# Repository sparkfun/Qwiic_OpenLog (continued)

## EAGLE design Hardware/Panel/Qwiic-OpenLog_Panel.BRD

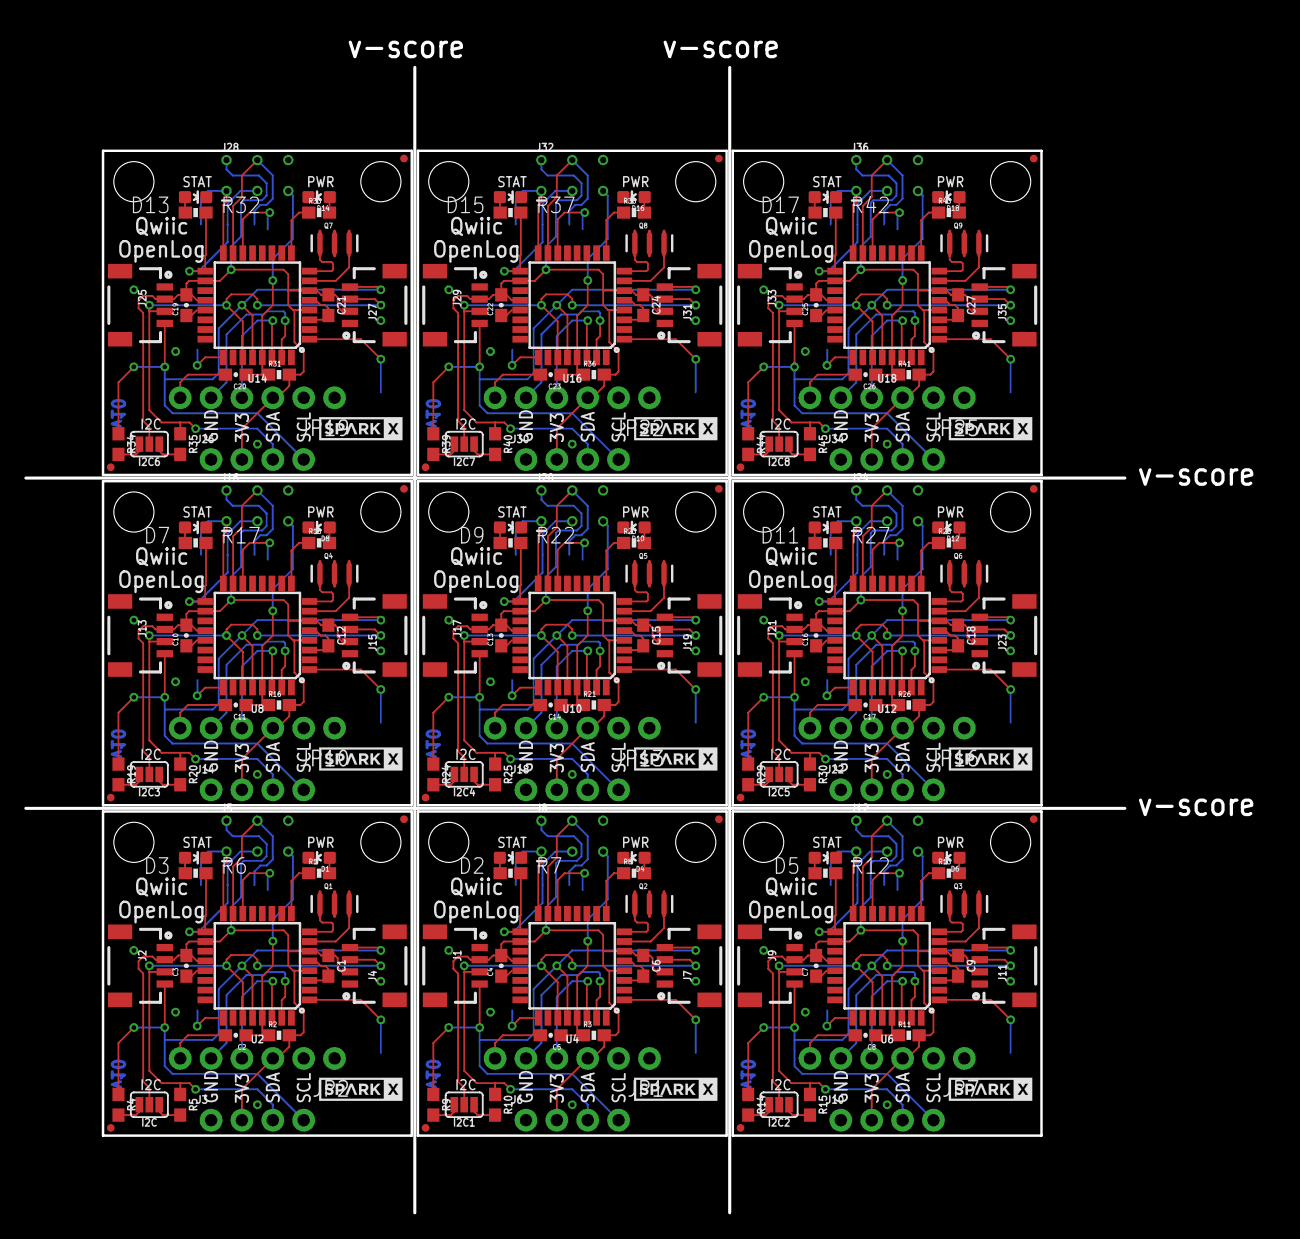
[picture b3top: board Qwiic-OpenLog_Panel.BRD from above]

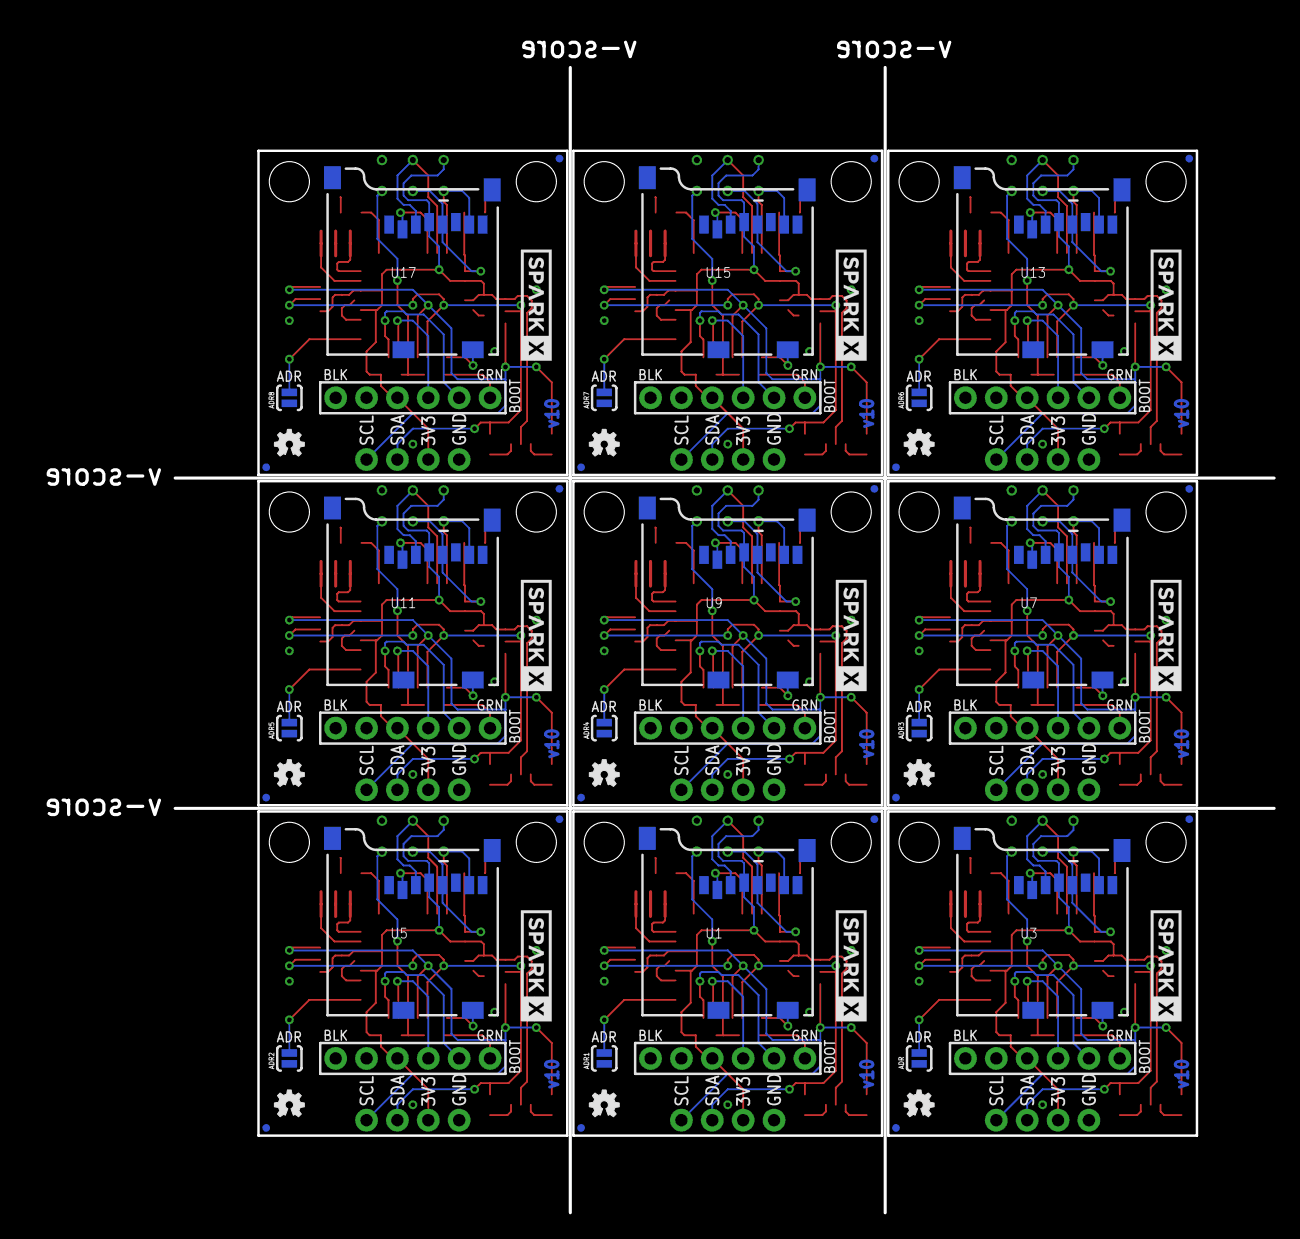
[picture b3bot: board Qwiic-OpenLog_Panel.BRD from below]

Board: 2 copper layers, 90.4 x 94.2 mm, 261 parts (54 on the bottom side), 189 nets.

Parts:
ADR, ADR1, ADR2, ADR3, ADR4, ADR5, ADR6, ADR7, ADR8: SJ_2S-NO
C1, C6, C9, C12, C15, C18, C21, C24, C27: 4.7uF; 0603
C2, C3, C4, C5, C7, C8, C10, C11, C13, C14, C16, C17, C19, C20, C22, C23, C25, C26: 0.1uF; 0603-CAP
D1, D4, D6, D8, D10, D12, D14, D16, D18: RED; LED-0603
D2, D3, D5, D7, D9, D11, D13, D15, D17: GREEN; LED-0603
FID1, FID2, FID3, FID4, FID5, FID6, FID7, FID8, FID9, FID10, FID11, FID12, FID13, FID14, FID15, FID16, FID17, FID18, FID19, FID20, FID21, FID22, FID23, FID24, FID25, FID26, FID27, FID28, FID29, FID30, FID31, FID32, FID33, FID34, FID35, FID36: FIDUCIALUFIDUCIAL; MICRO-FIDUCIAL
I2C, I2C1, I2C2, I2C3, I2C4, I2C5, I2C6, I2C7, I2C8: SMT-JUMPER_3_2-NC_PASTE_SILK
J1, J2, J4, J7, J9, J11, J13, J15, J17, J19, J21, J23, J25, J27, J29, J31, J33, J35: SMD; 1X04_1MM_RA
J3, J6, J10, J14, J18, J22, J26, J30, J34: PTH; 1X04_NO_SILK
J5, J8, J12, J16, J20, J24, J28, J32, J36: ISP; 2X3_TEST_POINTS
JP1, JP2, JP7, JP10, JP13, JP16, JP19, JP22, JP25: BOOT; 1X06_NO_SILK
JP3, JP4, JP5, JP6, JP8, JP9, JP11, JP12, JP14, JP15, JP17, JP18, JP20, JP21, JP23, JP24, JP26, JP27: STAND-OFF
LOGO1, LOGO2, LOGO3, LOGO4, LOGO5, LOGO6, LOGO7, LOGO8, LOGO9: OSHW-LOGOMINI; OSHW-LOGO-MINI
Q1, Q2, Q3, Q4, Q5, Q6, Q7, Q8, Q9: 16MHZ; RESONATOR-SMD
R1, R8, R13, R18, R23, R28, R33, R38, R43: 1K; 0603-RES
R2, R3, R11, R16, R21, R26, R31, R36, R41: 10K; 0603-RES
R4, R5, R9, R10, R14, R15, R19, R20, R24, R25, R29, R30, R34, R35, R39, R40, R44, R45: 2.2k; 0603
R6, R7, R12, R17, R22, R27, R32, R37, R42: 330; 0603-RES
U1, U3, U5, U7, U9, U11, U13, U15, U17: microSD Socket; MICRO-SD-SOCKET-PP
U2, U4, U6, U8, U10, U12, U14, U16, U18: ATMEGA328P_TQFP; TQFP32-08
U$1, U$4, U$6, U$8, U$10, U$12, U$14, U$16, U$18: SPARKX-LOGO4; SPARKX-MEDIUM
U$2, U$3, U$5, U$7, U$9, U$11, U$13, U$15, U$17: SPARKX-LOGO3; SPARKX-SMALL

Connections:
3.3V: C1.1, C3.2, I2C.2, J2.2, J3.2, J4.2, J5.2, JP2.3, R2.2, U2.4, U2.6, U2.18, U2.20, U3.VCC
3.3V1: C4.2, C6.1, I2C1.2, J1.2, J6.2, J7.2, J8.2, JP1.3, R3.2, U1.VCC, U4.4, U4.6, U4.18, U4.20
3.3V2: C7.2, C9.1, I2C2.2, J9.2, J10.2, J11.2, J12.2, JP7.3, R11.2, U5.VCC, U6.4, U6.6, U6.18, U6.20
3.3V3: C10.2, C12.1, I2C3.2, J13.2, J14.2, J15.2, J16.2, JP10.3, R16.2, U7.VCC, U8.4, U8.6, U8.18, U8.20
3.3V4: C13.2, C15.1, I2C4.2, J17.2, J18.2, J19.2, J20.2, JP13.3, R21.2, U9.VCC, U10.4, U10.6, U10.18, U10.20
3.3V5: C16.2, C18.1, I2C5.2, J21.2, J22.2, J23.2, J24.2, JP16.3, R26.2, U11.VCC, U12.4, U12.6, U12.18, U12.20
3.3V6: C19.2, C21.1, I2C6.2, J25.2, J26.2, J27.2, J28.2, JP19.3, R31.2, U13.VCC, U14.4, U14.6, U14.18, U14.20
3.3V7: C22.2, C24.1, I2C7.2, J29.2, J30.2, J31.2, J32.2, JP22.3, R36.2, U15.VCC, U16.4, U16.6, U16.18, U16.20
3.3V8: C25.2, C27.1, I2C8.2, J33.2, J34.2, J35.2, J36.2, JP25.3, R41.2, U17.VCC, U18.4, U18.6, U18.18, U18.20
ADDR: ADR.2, U2.1
ADDR1: ADR1.2, U4.1
ADDR2: ADR2.2, U6.1
ADDR3: ADR3.2, U8.1
ADDR4: ADR4.2, U10.1
ADDR5: ADR5.2, U12.1
ADDR6: ADR6.2, U14.1
ADDR7: ADR7.2, U16.1
ADDR8: ADR8.2, U18.1
CD: U2.25, U3.CD1
CD1: U1.CD1, U4.25
CD2: U5.CD1, U6.25
CD3: U7.CD1, U8.25
CD4: U9.CD1, U10.25
CD5: U11.CD1, U12.25
CD6: U13.CD1, U14.25
CD7: U15.CD1, U16.25
CD8: U17.CD1, U18.25
CS: U2.14, U3.CS
CS1: U1.CS, U4.14
CS2: U5.CS, U6.14
CS3: U7.CS, U8.14
CS4: U9.CS, U10.14
CS5: U11.CS, U12.14
CS6: U13.CS, U14.14
CS7: U15.CS, U16.14
CS8: U17.CS, U18.14
DTR: C2.2, JP2.6
DTR1: C5.2, JP1.6
DTR2: C8.2, JP7.6
DTR3: C11.2, JP10.6
DTR4: C14.2, JP13.6
DTR5: C17.2, JP16.6
DTR6: C20.2, JP19.6
DTR7: C23.2, JP22.6
DTR8: C26.2, JP25.6
GND: ADR.1, C1.2, C3.1, D1.C, D3.C, J2.1, J3.1, J4.1, J5.6, JP2.1, JP2.2, Q1.2, U2.3, U2.5, U2.21, U3.GND, U3.GND1, U3.GND3
GND1: ADR1.1, C4.1, C6.2, D2.C, D4.C, J1.1, J6.1, J7.1, J8.6, JP1.1, JP1.2, Q2.2, U1.GND, U1.GND1, U1.GND3, U4.3, U4.5, U4.21
GND2: ADR2.1, C7.1, C9.2, D5.C, D6.C, J9.1, J10.1, J11.1, J12.6, JP7.1, JP7.2, Q3.2, U5.GND, U5.GND1, U5.GND3, U6.3, U6.5, U6.21
GND3: ADR3.1, C10.1, C12.2, D7.C, D8.C, J13.1, J14.1, J15.1, J16.6, JP10.1, JP10.2, Q4.2, U7.GND, U7.GND1, U7.GND3, U8.3, U8.5, U8.21
GND4: ADR4.1, C13.1, C15.2, D9.C, D10.C, J17.1, J18.1, J19.1, J20.6, JP13.1, JP13.2, Q5.2, U9.GND, U9.GND1, U9.GND3, U10.3, U10.5, U10.21
GND5: ADR5.1, C16.1, C18.2, D11.C, D12.C, J21.1, J22.1, J23.1, J24.6, JP16.1, JP16.2, Q6.2, U11.GND, U11.GND1, U11.GND3, U12.3, U12.5, U12.21
GND6: ADR6.1, C19.1, C21.2, D13.C, D14.C, J25.1, J26.1, J27.1, J28.6, JP19.1, JP19.2, Q7.2, U13.GND, U13.GND1, U13.GND3, U14.3, U14.5, U14.21
GND7: ADR7.1, C22.1, C24.2, D15.C, D16.C, J29.1, J30.1, J31.1, J32.6, JP22.1, JP22.2, Q8.2, U15.GND, U15.GND1, U15.GND3, U16.3, U16.5, U16.21
GND8: ADR8.1, C25.1, C27.2, D17.C, D18.C, J33.1, J34.1, J35.1, J36.6, JP25.1, JP25.2, Q9.2, U17.GND, U17.GND1, U17.GND3, U18.3, U18.5, U18.21
MISO: J5.1, U2.16, U3.DO
MISO1: J8.1, U1.DO, U4.16
MISO2: J12.1, U5.DO, U6.16
MISO3: J16.1, U7.DO, U8.16
MISO4: J20.1, U9.DO, U10.16
MISO5: J24.1, U11.DO, U12.16
MISO6: J28.1, U13.DO, U14.16
MISO7: J32.1, U15.DO, U16.16
MISO8: J36.1, U17.DO, U18.16
MOSI: J5.4, U2.15, U3.DI
MOSI1: J8.4, U1.DI, U4.15
MOSI2: J12.4, U5.DI, U6.15
MOSI3: J16.4, U7.DI, U8.15
MOSI4: J20.4, U9.DI, U10.15
MOSI5: J24.4, U11.DI, U12.15
MOSI6: J28.4, U13.DI, U14.15
MOSI7: J32.4, U15.DI, U16.15
MOSI8: J36.4, U17.DI, U18.15
unnamed: Q1.1, U2.8
unnamed: Q1.3, U2.7
unnamed: D1.A, R1.2
unnamed: R1.1, U2.9
unnamed: I2C.1, R5.2
unnamed: I2C.3, R4.2
unnamed: D3.A, R6.2
unnamed: D2.A, R7.2
unnamed: Q2.1, U4.8
unnamed: Q2.3, U4.7
unnamed: D4.A, R8.2
unnamed: R8.1, U4.9
unnamed: I2C1.1, R10.2
unnamed: I2C1.3, R9.2
unnamed: D5.A, R12.2
unnamed: Q3.1, U6.8
unnamed: Q3.3, U6.7
unnamed: D6.A, R13.2
unnamed: R13.1, U6.9
unnamed: I2C2.1, R15.2
unnamed: I2C2.3, R14.2
unnamed: D7.A, R17.2
unnamed: Q4.1, U8.8
unnamed: Q4.3, U8.7
unnamed: D8.A, R18.2
unnamed: R18.1, U8.9
unnamed: I2C3.1, R20.2
unnamed: I2C3.3, R19.2
unnamed: D9.A, R22.2
unnamed: Q5.1, U10.8
unnamed: Q5.3, U10.7
unnamed: D10.A, R23.2
unnamed: R23.1, U10.9
unnamed: I2C4.1, R25.2
unnamed: I2C4.3, R24.2
unnamed: D11.A, R27.2
unnamed: Q6.1, U12.8
unnamed: Q6.3, U12.7
unnamed: D12.A, R28.2
unnamed: R28.1, U12.9
unnamed: I2C5.1, R30.2
unnamed: I2C5.3, R29.2
unnamed: D13.A, R32.2
unnamed: Q7.1, U14.8
unnamed: Q7.3, U14.7
unnamed: D14.A, R33.2
unnamed: R33.1, U14.9
unnamed: I2C6.1, R35.2
unnamed: I2C6.3, R34.2
unnamed: D15.A, R37.2
unnamed: Q8.1, U16.8
unnamed: Q8.3, U16.7
unnamed: D16.A, R38.2
unnamed: R38.1, U16.9
unnamed: I2C7.1, R40.2
unnamed: I2C7.3, R39.2
unnamed: D17.A, R42.2
unnamed: Q9.1, U18.8
unnamed: Q9.3, U18.7
unnamed: D18.A, R43.2
unnamed: R43.1, U18.9
unnamed: I2C8.1, R45.2
unnamed: I2C8.3, R44.2
RST: C2.1, J5.5, R2.1, U2.29
RST1: C5.1, J8.5, R3.1, U4.29
RST2: C8.1, J12.5, R11.1, U6.29
RST3: C11.1, J16.5, R16.1, U8.29
RST4: C14.1, J20.5, R21.1, U10.29
RST5: C17.1, J24.5, R26.1, U12.29
RST6: C20.1, J28.5, R31.1, U14.29
RST7: C23.1, J32.5, R36.1, U16.29
RST8: C26.1, J36.5, R41.1, U18.29
RXI: JP2.4, U2.30
RXI1: JP1.4, U4.30
RXI2: JP7.4, U6.30
RXI3: JP10.4, U8.30
RXI4: JP13.4, U10.30
RXI5: JP16.4, U12.30
RXI6: JP19.4, U14.30
RXI7: JP22.4, U16.30
RXI8: JP25.4, U18.30
SCK: J5.3, R6.1, U2.17, U3.SCLK
SCK1: J8.3, R7.1, U1.SCLK, U4.17
SCK2: J12.3, R12.1, U5.SCLK, U6.17
SCK3: J16.3, R17.1, U7.SCLK, U8.17
SCK4: J20.3, R22.1, U9.SCLK, U10.17
SCK5: J24.3, R27.1, U11.SCLK, U12.17
SCK6: J28.3, R32.1, U13.SCLK, U14.17
SCK7: J32.3, R37.1, U15.SCLK, U16.17
SCK8: J36.3, R42.1, U17.SCLK, U18.17
SCL: J2.4, J3.4, J4.4, R4.1, U2.28
SCL1: J1.4, J6.4, J7.4, R9.1, U4.28
SCL2: J9.4, J10.4, J11.4, R14.1, U6.28
SCL3: J13.4, J14.4, J15.4, R19.1, U8.28
SCL4: J17.4, J18.4, J19.4, R24.1, U10.28
SCL5: J21.4, J22.4, J23.4, R29.1, U12.28
SCL6: J25.4, J26.4, J27.4, R34.1, U14.28
SCL7: J29.4, J30.4, J31.4, R39.1, U16.28
SCL8: J33.4, J34.4, J35.4, R44.1, U18.28
SDA: J2.3, J3.3, J4.3, R5.1, U2.27
SDA1: J1.3, J6.3, J7.3, R10.1, U4.27
SDA2: J9.3, J10.3, J11.3, R15.1, U6.27
SDA3: J13.3, J14.3, J15.3, R20.1, U8.27
SDA4: J17.3, J18.3, J19.3, R25.1, U10.27
SDA5: J21.3, J22.3, J23.3, R30.1, U12.27
SDA6: J25.3, J26.3, J27.3, R35.1, U14.27
SDA7: J29.3, J30.3, J31.3, R40.1, U16.27
SDA8: J33.3, J34.3, J35.3, R45.1, U18.27
TXO: JP2.5, U2.31
TXO1: JP1.5, U4.31
TXO2: JP7.5, U6.31
TXO3: JP10.5, U8.31
TXO4: JP13.5, U10.31
TXO5: JP16.5, U12.31
TXO6: JP19.5, U14.31
TXO7: JP22.5, U16.31
TXO8: JP25.5, U18.31

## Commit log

2018-02-27 Updating readme
2018-02-28 More examples. Finishing up v1.0.
2018-03-01 Readme photo update. Adding production programming tools.
2018-03-07 Removing examples. They are now in library.
2018-07-18 Updating with Buzzard labels
2018-07-30 Adding programming CLI readme
2018-11-16 Fix readme image
2018-11-16 Add programming batch file
2019-02-05 Adding pull up on CS pin to allow for easier ISP programming.
2019-02-05 Add v12 production panel
2019-02-05 Revmoving programming files. This is now done directly in the production jig.
2019-02-06 v2.0 firmware, now with a register map!
2019-05-02 ~160x faster write speed, ~2x effective storage size, may break compatibility with older code
    Changed writeFile so it:
    -doesn't sync to SD card every byte written
    -doesn't write an extra null character after every byte specified by the user to be written. sizeof(*myData) does *not* return the length of the string. It returns the size of the type pointer to cha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
2019-05-09 updating firmware version that is read from openlog to 3.01
2019-05-09 uploading precompiled binary
2023-05-05 Create README.md
    Add library dependency information for firmware
2023-05-12 Update README.md
    Update instructions
